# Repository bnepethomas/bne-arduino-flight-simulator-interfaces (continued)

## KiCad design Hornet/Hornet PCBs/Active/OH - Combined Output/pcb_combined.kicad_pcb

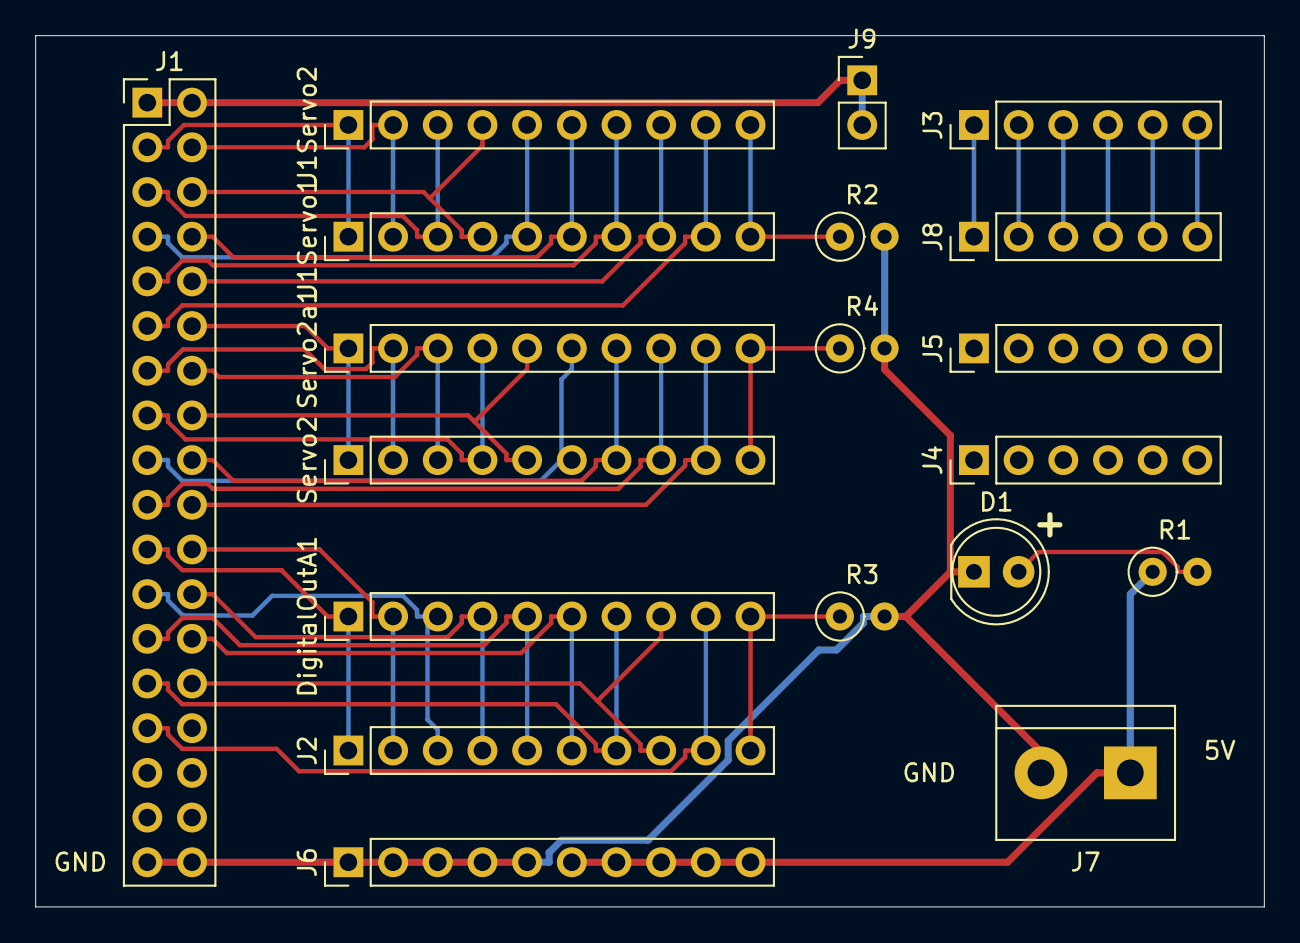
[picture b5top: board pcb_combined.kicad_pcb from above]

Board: 2 copper layers, 69.8 x 49.5 mm, 19 parts (0 on the bottom side), 40 nets.

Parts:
D1: LED; LED_D5.0mm
DigitalOutA1: Digitial Out; PinHeader_1x10_P2.54mm_Vertical
J1: Arduino Mega; PinHeader_2x18_P2.54mm_Vertical
J1Servo1: Servo 1a; PinHeader_1x10_P2.54mm_Vertical
J1Servo2: Servo 1b; PinHeader_1x10_P2.54mm_Vertical
J2: Digital Out; PinHeader_1x10_P2.54mm_Vertical
J3: SPI In; PinHeader_1x06_P2.54mm_Vertical
J4: Spare 1; PinHeader_1x06_P2.54mm_Vertical
J5: Spare 2; PinHeader_1x06_P2.54mm_Vertical
J6: Gnd Pwr; PinHeader_1x10_P2.54mm_Vertical
J7: Aux Pwr In; TerminalBlock_bornier-2_P5.08mm
J8: SPI Out; PinHeader_1x06_P2.54mm_Vertical
J9: Mega 5V; PinHeader_1x02_P2.54mm_Vertical
R1, R2, R3, R4: R_US; R_Axial_DIN0207_L6.3mm_D2.5mm_P2.54mm_Vertical
Servo2: Servo 2; PinHeader_1x10_P2.54mm_Vertical
Servo2a1: Servo 2a; PinHeader_1x10_P2.54mm_Vertical

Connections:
+5V: J6.6, J6.7, J6.8, J6.9, J6.10, J7.1, R1.1
/Mega5V: J1.1, J1.2, J9.1, J9.2
GND: D1.1, J1.35, J1.36, J6.1, J6.2, J6.3, J6.4, J6.5, J7.2, R2.2, R3.2, R4.2
unnamed: D1.2, R1.2
unnamed: DigitalOutA1.1, J1.21, J2.1
unnamed: DigitalOutA1.2, J1.22, J2.2
unnamed: DigitalOutA1.3, J1.23, J2.3
unnamed: DigitalOutA1.4, J1.24, J2.4
unnamed: DigitalOutA1.5, J1.25, J2.5
unnamed: DigitalOutA1.6, J1.26, J2.6
unnamed: DigitalOutA1.7, J1.27, J2.7
unnamed: DigitalOutA1.8, J1.28, J2.8
unnamed: DigitalOutA1.9, J1.29, J2.9
unnamed: DigitalOutA1.10, J2.10, R3.1
unnamed: J1.3, J1Servo1.1, J1Servo2.1
unnamed: J1.4, J1Servo1.2, J1Servo2.2
unnamed: J1.5, J1Servo1.3, J1Servo2.3
unnamed: J1.6, J1Servo1.4, J1Servo2.4
unnamed: J1.7, J1Servo1.5, J1Servo2.5
unnamed: J1.8, J1Servo1.6, J1Servo2.6
unnamed: J1.9, J1Servo1.7, J1Servo2.7
unnamed: J1.10, J1Servo1.8, J1Servo2.8
unnamed: J1.11, J1Servo1.9, J1Servo2.9
unnamed: J1.12, Servo2.1, Servo2a1.1
unnamed: J1.13, Servo2.2, Servo2a1.2
unnamed: J1.14, Servo2.3, Servo2a1.3
unnamed: J1.15, Servo2.4, Servo2a1.4
unnamed: J1.16, Servo2.5, Servo2a1.5
unnamed: J1.17, Servo2.6, Servo2a1.6
unnamed: J1.18, Servo2.7, Servo2a1.7
unnamed: J1.19, Servo2.8, Servo2a1.8
unnamed: J1.20, Servo2.9, Servo2a1.9
unnamed: J1Servo1.10, J1Servo2.10, R2.1
unnamed: J3.1, J8.1
unnamed: J3.2, J8.2
unnamed: J3.3, J8.3
unnamed: J3.4, J8.4
unnamed: J3.5, J8.5
unnamed: J3.6, J8.6
unnamed: R4.1, Servo2.10, Servo2a1.10

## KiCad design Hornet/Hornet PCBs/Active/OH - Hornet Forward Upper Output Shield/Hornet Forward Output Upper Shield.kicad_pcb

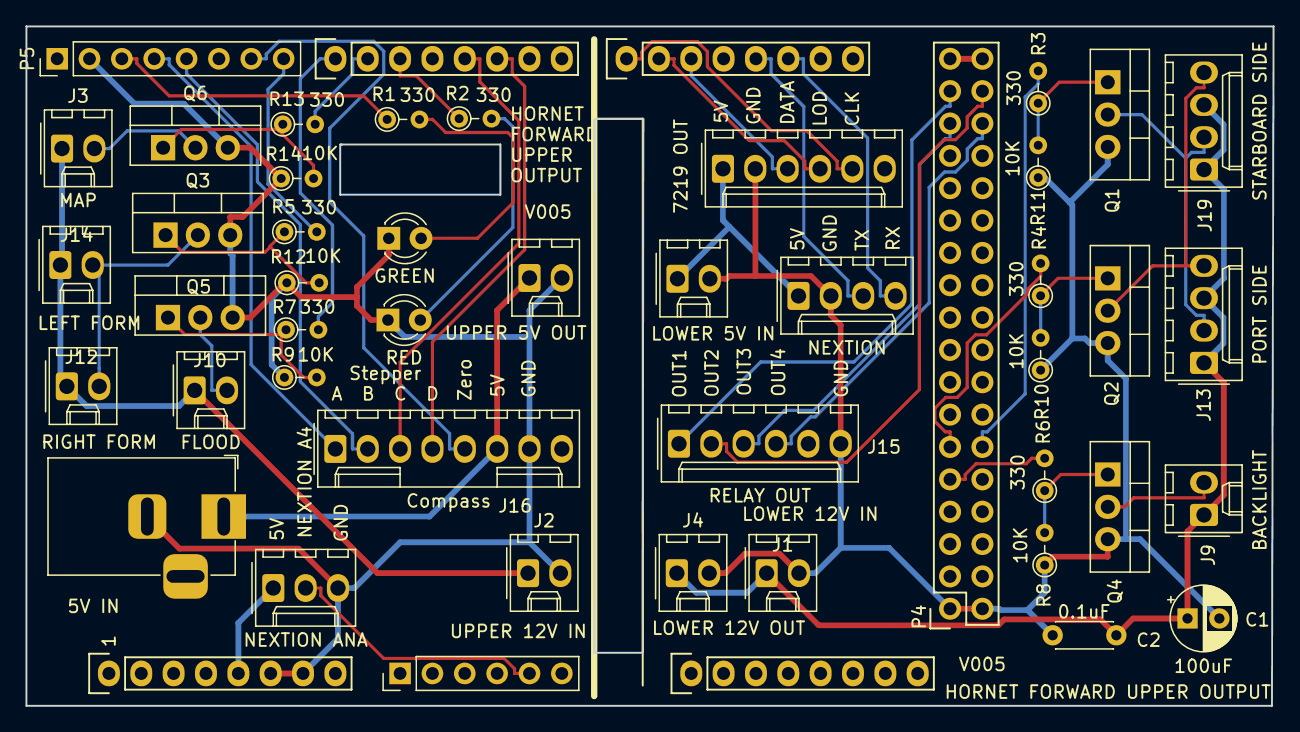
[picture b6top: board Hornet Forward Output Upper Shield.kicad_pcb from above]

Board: 2 copper layers, 97.9 x 53.3 mm, 49 parts (0 on the bottom side), 45 nets.

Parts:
C1: 100uF; CP_Radial_D5.0mm_P2.50mm
C2: 0.1uF; C_Disc_D4.3mm_W1.9mm_P5.00mm
D1: GREEN; LED_D3.0mm
D2: RED; LED_D3.0mm
J1: LOWER 12V IN; Molex_1x02_P2.54mm_Vertical
J2: UPPER 12V IN; Molex_1x02_P2.54mm_Vertical
J3: MAP; Molex_1x02_P2.54mm_Vertical
J4: LOWER 12V OUT; Molex_1x02_P2.54mm_Vertical
J5: LOWER 5V IN; Molex_1x02_P2.54mm_Vertical
J6: UPPER 5V OUT; Molex_1x02_P2.54mm_Vertical
J7: NEXTION; Molex_1x04_P2.54mm_Vertical
J8: 7219 OUT; Molex_1x06_P2.54mm_Vertical
J9: BACKLIGHT; Molex_1x02_P2.54mm_Vertical
J10: FLOOD; Molex_1x02_P2.54mm_Vertical
J11: 5V IN; BarrelJack_Horizontal
J12: RIGHT FORM; Molex_1x02_P2.54mm_Vertical
J13: PORT SIDE; Molex_1x04_P2.54mm_Vertical
J14: LEFT FORM; Molex_1x02_P2.54mm_Vertical
J15: RELAY OUT; Molex_1x06_P2.54mm_Vertical
J16: Compass; Molex_1x08_P2.54mm_Vertical
J18: NEXTION ANA; Molex_1x03_P2.54mm_Vertical
J19: STARBOARD SIDE; Molex_1x04_P2.54mm_Vertical
P1: Power; Socket_Strip_Arduino_1x08
P2: Analog; PinHeader_1x06_P2.54mm_Vertical
P3: Analog; Socket_Strip_Arduino_1x08
P4: Digital; Socket_Strip_Arduino_2x18
P5: PWM; PinHeader_1x08_P2.54mm_Vertical
P6: PWM; Socket_Strip_Arduino_1x08
P7: Communication; Socket_Strip_Arduino_1x08
Q1, Q2, Q3, Q4, Q5, Q6: IRF1405PBF; TO-220-3_Vertical
R1, R2, R3, R4, R5, R6, R7, R13: 330; PT_R_Axial_DIN0204_L3.6mm_D1.6mm_P2.54mm_Vertical
R8, R9, R10, R11, R12, R14: 10K; PT_R_Axial_DIN0204_L3.6mm_D1.6mm_P2.54mm_Vertical

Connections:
+5V: P4.35, P4.36
+5VL: J18.1, P1.5
+12V: C1.1, C2.1, J1.1, J4.1, J9.1, J13.1, J13.3, J19.1, J19.3
+12VA: J2.1, J3.1, J10.1, J12.1, J14.1
/14(Tx3): J8.5, P7.1
/15(Rx3): J8.4, P7.2
/16(Tx2): J8.3, P7.3
/18(Tx1): J7.3, P7.5
/19(Rx1): J7.4, P7.6
/22: J15.1, P4.33
/23: J15.2, P4.34
/24: J15.3, P4.31
/25: J15.4, P4.32
/44: P4.11, R4.2
/45: P4.12, R3.2
/46: P4.9, R6.2
/A4: J18.2, P2.5
/Compass_Stepper_A: J16.1, P5.4
/Compass_Stepper_B: J16.2, P5.5
/Compass_Stepper_C: J16.3, P6.5
/Compass_Stepper_D: J16.4, P6.6
/Compass_Zero_Sensor: J16.5, P5.7
/D5: P6.3, R2.1
/D6: P6.2, R13.2
/D7: P6.1, R7.2
/D8: P5.8, R5.2
/D13: P5.3, R1.1
/FORMATION_LIGHTS_NEG: J12.2, J14.2, Q3.2
/LOWER_OUTPUT_5V: J5.1, J7.1, J8.1
/NAV_LIGHTS_NEG: J13.2, J19.2, Q1.2
/STROBE_LIGHTS_NEG: J13.4, J19.4, Q2.2
/UPPER_OUTPUT_5V: J6.1, J11.1, J16.6
GND: C1.2, C2.2, J1.2, J4.2, J5.2, J7.2, J8.2, J15.6, P4.1, P4.2, Q1.3, Q2.3, Q4.3, R8.1, R10.1, R11.1
GNDD: D1.1, D2.1, J2.2, J6.2, J11.2, J16.7, J18.3, P1.6, P1.7, P5.2, Q3.3, Q5.3, Q6.3, R9.1, R12.1, R14.1
unnamed: D1.2, R1.2
unnamed: D2.2, R2.2
unnamed: J3.2, Q6.2
unnamed: J9.2, Q4.2
unnamed: J10.2, Q5.2
unnamed: Q1.1, R3.1, R11.2
unnamed: Q2.1, R4.1, R10.2
unnamed: Q3.1, R5.1, R12.2
unnamed: Q4.1, R6.1, R8.2
unnamed: Q5.1, R7.1, R9.2
unnamed: Q6.1, R13.1, R14.2

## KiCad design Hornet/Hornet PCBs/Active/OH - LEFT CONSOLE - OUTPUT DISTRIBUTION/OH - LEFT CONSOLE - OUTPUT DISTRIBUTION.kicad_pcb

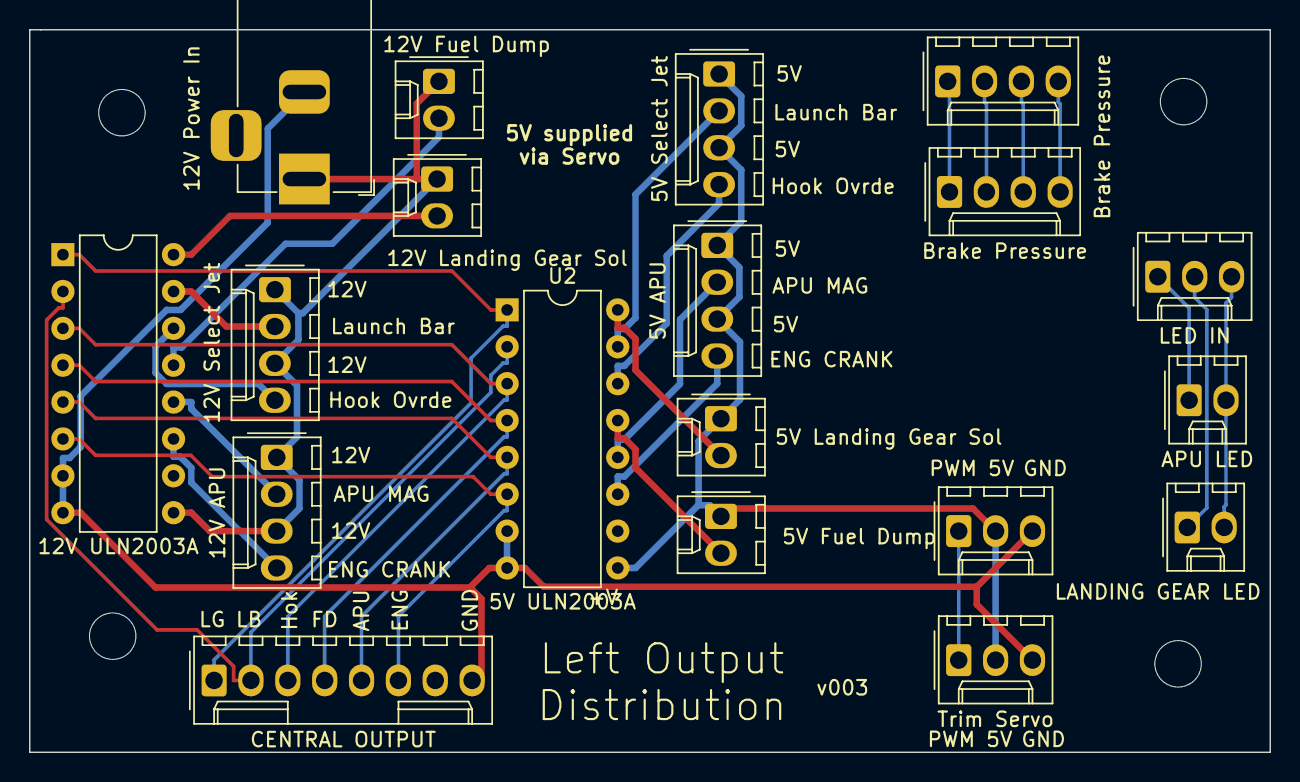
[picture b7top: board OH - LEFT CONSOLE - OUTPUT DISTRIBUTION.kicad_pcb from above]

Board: 2 copper layers, 85.5 x 49.8 mm, 23 parts (0 on the bottom side), 29 nets.

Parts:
H1, H2, H3, H4: MountingHole; MountingHole_3.2mm_M3
J1: CENTRAL OUTPUT; Molex_1x08_P2.54mm_Vertical
J2: 12V Power In; BarrelJack_Horizontal
J3: 5V Landing Gear Sol; Molex_1x02_P2.54mm_Vertical
J4: APU LED; Molex_1x02_P2.54mm_Vertical
J5: 5V Fuel Dump; Molex_1x02_P2.54mm_Vertical
J6: 5V Select Jet; Molex_1x04_P2.54mm_Vertical
J7, J12: Brake Pressure; Molex_1x04_P2.54mm_Vertical
J8: LANDING GEAR LED; Molex_1x02_P2.54mm_Vertical
J9: 12V Landing Gear Sol; Molex_1x02_P2.54mm_Vertical
J10: 12V Select Jet; Molex_1x04_P2.54mm_Vertical
J11: 12V Fuel Dump; Molex_1x02_P2.54mm_Vertical
J13: 12V APU; Molex_1x04_P2.54mm_Vertical
J14: 5V APU; Molex_1x04_P2.54mm_Vertical
J15, J17: Trim Servo; Molex_1x03_P2.54mm_Vertical
J16: LED IN; Molex_1x03_P2.54mm_Vertical
U1: 12V ULN2003A; DIP-16_W7.62mm
U2: 5V ULN2003A; DIP-16_W7.62mm

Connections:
/5V_APU_Mag: J14.2, U2.12
/5V_Engine_Crank_Mag: J14.4, U2.11
/5V_Fuel_Dump_Mag: J5.2, U2.13
/5V_Hook_Bypass_Mag: J6.4, U2.14
/5V_Landing_Gear_Sol: J3.2, U2.16
/5V_Launch_Bar_Mag: J6.2, U2.15
/12V_APU_Mag: J13.2, U1.12
/12V_Engine_Crank_Mag: J13.4, U1.11
/12V_Fuel_Dump_Mag: J11.2, U1.13
/12V_Hook_Bypass_Mag: J10.4, U1.14
/12V_Landing_Gear_Sol: J9.2, U1.16
/12V_Launch_Bar_Mag: J10.2, U1.15
/+12V: J2.1, J9.1, J10.1, J10.3, J11.1, J13.1, J13.3, U1.9
/GND: J1.8, J2.2, J15.3, J17.3, U1.7, U1.8, U2.7, U2.8
/In_APU_Mag: J1.5, U1.5, U2.5
/In_Engine_Crank_Mag: J1.6, U1.6, U2.6
/In_Fuel_Dump_Mag: J1.4, U1.4, U2.4
/In_Hook_Bypass_Mag: J1.3, U1.3, U2.3
/In_Landing_Gear_Sol: J1.1, U1.1, U2.1
/In_Launch_Bar_Mag: J1.2, U1.2, U2.2
/LEDCOL1: J4.2, J8.2, J16.3
/LEDROW1: J4.1, J16.1
/LEDROW2: J8.1, J16.2
/SERVO_5V: J3.1, J5.1, J6.1, J6.3, J14.1, J14.3, J15.2, J17.2, U2.9
/SERVO_PWM: J15.1, J17.1
unnamed: J7.1, J12.1
unnamed: J7.2, J12.2
unnamed: J7.3, J12.3
unnamed: J7.4, J12.4
